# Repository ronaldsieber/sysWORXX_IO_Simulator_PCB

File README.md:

# sysWORXX IO Simulator

**KiCad Projekt des sysWORXX IO Simulator sowie Node-RED-Flow für das sysWORXX CTR-700, um die grundlegende Funktionalität des IO Simulator zu veranschaulichen.**

Der *sysWORXX IO Simulator* stellt verschiedene Peripherie-Elemente bereit, um Experimente sowie Test- und Inbetriebnahme von Softwareprojekten auf dem *sysWORXX CTR-700* zu vereinfachen.

## IO Simulator Board Features

Der *sysWORXX IO Simulator* umfasst folgende Peripherie-Elemente:
- 4x Digital Input 24V (Push-Button)
- 4x Digital Output 24V (LED)
- 4x Analog Input 0..10V (2x Poti, 1x Fotoelement, 1x Reflexkoppler)
- 1x A/B Encoder

![\[kicad_3d_model\]](Documentation/sysWORXX_IO_Simulator_PCB.3d-model.png)

## sysWORXX CTR-700

Der *sysWORXX CTR-700* ist ein Linux-basierter Controller mit offener Architektur, der softwareseitig stark dem Raspberry Pi ähnelt und die IO-Peripherie einer klassischen SPS-Steuerung unterstützt (DI/DO 24V, AI 0..10V, AI 4..20mA, Relais 230VAC, UART/RS232/RS485, ETH, CAN):

Hersteller Seite:
https://www.systec-electronic.com/produkte/industrial-internet-of-things/sysworxx-ctr-700

Bezugsquelle:
https://www.conrad.de/de/p/sysworxx-ctr-700-industrial-controller-industriesteuerung-sps-iot-leistungsstarke-steuerung-mqtt-node-red-805716248.html

![\[sysWORXX CTR-700\]](Documentation/sysWORXX_CTR-700.png)

Der CTR-700 unterstützt folgende Programmiersprachen:
- C/C++
- C#
- Java
- Python
- Node-RED
- IEC 61131-3

## sysWORXX IO Simulator

Der *sysWORXX IO Simulator* basiert auf einer vierlagigen Leiterplatte im Euro-Platinen Format (160x100 mm), von der jedoch nur 3 Ebenen benutz sind (Oberseite ohne Leiterbahnen). Die Platine ist einseitig bestückt und verwendet nur sehr einfach zu lötende THT Bauteile (Through Hole Technology). Der *IO Simulator* kann somit leicht auch von Schülern und Bastlern aufgebaut werden.

Die Werte aller Bauteile sind im [Schaltplan](Documentation/sysWORXX_IO_Simulator_PCB_Schematic.pdf) spezifiziert.

![\[sysWORXX IO Simulator\]](Documentation/sysWORXX_IO_Simulator.jpg)

**Verbindung zwischen IO Simulator und CTR-700**

Alle Anschlüsse des *IO Simulator* sind entsprechende ihrer Funktionalitäten gruppiert (DI, DO, AI, Enc). Die Beschriftung an den Schraubklemmenblöcken des *IO Simulator* entspricht exakt den Bezeichnungen am *CTR-700*. Es müssen einfach nur die Signale mit gleichen Bezeichnungen zwischen beiden Baugruppen verbunden werden.

![\[Connector\]](Documentation/sysWORXX_IO_Simulator_Connector.png)
| IO Simulator | -> | CTR-700 |
|--|--|--|
| IO Simulator [DI0] | -> | CTR-700 [DI0] |
| ... | -> | ... |
| IO Simulator [DI3] | -> | CTR-700 [DI3] |
| IO Simulator [DI14] | -> | CTR-700 [DI14] |
| IO Simulator [DI15] | -> | CTR-700 [DI15] |
| IO Simulator [DO0] | -> | CTR-700 [DO0] |
| ... | -> | ... |
| IO Simulator [DO3] | -> | CTR-700 [DO3] |
| IO Simulator [AI0] | -> | CTR-700 [AI0] |
| ... | -> | ... |
| IO Simulator [AI3] | -> | CTR-700 [AI3] |

Für den professionellen Einsatz als Industriesteuerung besitzt das *sysWORXX CTR-700* jeweils getrennte Spannungs-Domains für CPU-Teil (24V/GND), Digital In (24V/GND), Digital Out (24V/GND) und Analog In (GND). In typischen Test- und Experimentierumgebungen kommt jedoch nur ein 24V Netzteil zum Einsatz, aus dem alle Domains parallel versorgt werden (jeweils alle 24V Anschlüsse sowie alle GND Anschlüsse parallel geschalten). An diese Domain sind auch 24V und GND des *IO Simulator* mit anzubinden. 

**IO Simulator Details**

Die Peripherie für digitale Ein- und Ausgänge (Push-Button, LED, A/B Encoder) nutzt direkt die 24V Spannungsversorgung des *IO Simulators*. Für die Peripherie der analogen Eingänge stellt VR1 (78L12) eine eigene 12V Domain bereit. Die analogen Eingänge des *CTR-700* sind nominell für 0..10V spezifiziert, sie lösen jedoch bis 11.64V auf, um auch Übersteuerungen erkennen und behandeln zu können.

Das Board ist mit verschiedenfarbigen Tasterkappen und LEDs bestückt (siehe Foto oben). Bei den LEDs wird für die blaue LED D103 ein Vorwiderstand von 4k7 verwendet, während die Vorwiderstände der anderen 3 LEDs (D100/rot, D101/grün, D102/gelb) mit 2k4 nur etwa halb so groß dimensioniert sind. Dadurch wird die blaue LED D103 optisch in ihrer Helligkeit an die anderen, deutlich dunkleren LEDs angeglichen.

Der Zweig OPT1 (OPT1, R202, R212) kann mit einem Fotowiderstand vom Typ PDV-P8104 (wie im [Schaltplan](Documentation/sysWORXX_IO_Simulator_PCB_Schematic.pdf)  angegeben) oder alternativ mit einer Fotodiode vom Typ BPW34 bestückt werden. Je nach Variante ist der Wert von R202 entsprechend anzupassen:

| OPT1 | R202 |
|--|--|
| PDV-P8104 | 20k |
| BPW34 | 200k |

Das Footprint von OPT1 ist als Combi-Shape ausgeführt, auf dem sich sowohl ein Fotowiderstand PDV-P8104 als eine Fotodiode BPW34 bestücken lassen.

**KiCad Schaltplansymbole und Footprints**

Für den *sysWORXX IO Simulator* wurden einige Schaltplansymbole und Footprints neu erstellt bzw. modifiziert. Diese sind im Repository im Zweig [KiCad_Components/usrlib](KiCad_Components/usrlib) abgelegt.

**Bezugsquellen**

In der [Stückliste](Documentation/sysWORXX_IO_Simulator_PCB_BoM.pdf) (BoM, Bill of Material) sind für alle Komponenten mögliche Bezugsquellen (incl. Bestellnummer) angegeben. Bei einer Suche im Internet findet man zudem leicht mehrere PCB Hersteller, die direkt das KiCad Layout File *sysWORXX_IO_Simulator_PCB.kicad_pcb* importieren können. Die PCBs erhält man dann mit Bestückungsdruck auf der Oberseite nach wenigen Tagen per Post zugeschickt. Eine mögliche direkte Bezugsquelle der Platine ist z.B. hier:

https://aisler.net/p/VOPTYJUX

## Node-RED Inbetriebnahme-Software

Test- und Inbetriebnahme des *sysWORXX IO Simulator* unterstützt der Node-RED Flow [CTR-700_IO_Periphery.json](Node-RED_Flow/CTR-700_IO_Periphery.json). Er bedient alle Komponenten des Simulators und stellt die aktuellen Werte auf einem Dashboard dar.

![\[Node-RED Inbetriebnahme Flow\]](Documentation/Node-RED_Editor.png)

Der Node-RED Flow [CTR-700_IO_Periphery.json](Node-RED_Flow/CTR-700_IO_Periphery.json) ist wie folgt in das Node-RED auf dem *sysWORXX CTR-700* zu importieren:

    Node-RED Menu -> Import -> Zwischenablage -> Button "Select a File to Import"

Um den Inbetriebnahme Flow nutzen zu können, muss zusätzlich die Node-Bibliothek `node-red-contrib-ctr700-io` auf dem *CTR-700* installiert sein. Diese wird bei Bedarf wie folgt installiert:

    Node-RED Menu -> Palette verwalten -> Tab "installieren" -> im Suchfeld "node-red-contrib-ctr700-io" eintragen -> Suchergebnis markieren und installieren

Nach dem Deploy auf das *CTR-700* wird der Flow auf dem Gerät ausgeführt und das Node-RED Dashboard visualisiert die aktuellen Werte der IO-Peripherie.

![\[Node-RED Dashboard\]](Documentation/Node-RED_Dashboard.png)

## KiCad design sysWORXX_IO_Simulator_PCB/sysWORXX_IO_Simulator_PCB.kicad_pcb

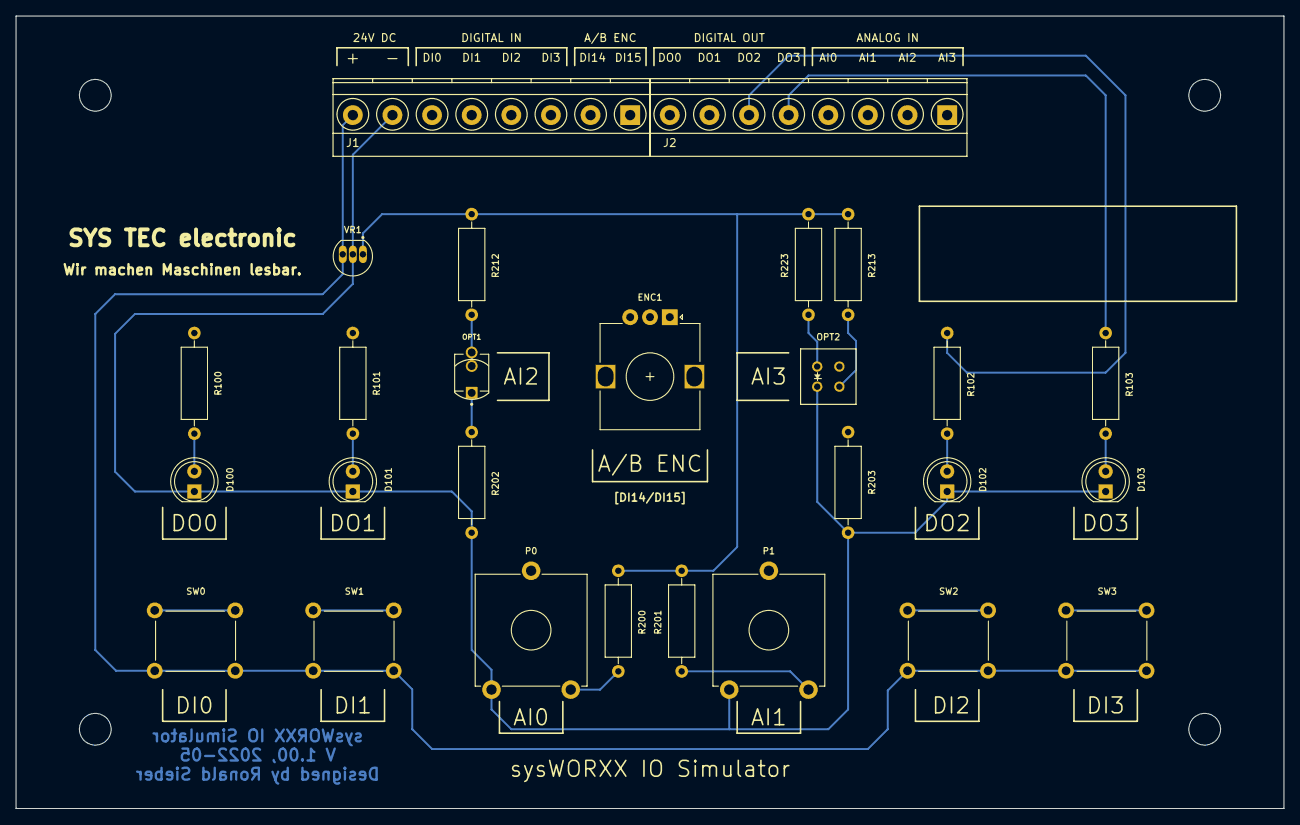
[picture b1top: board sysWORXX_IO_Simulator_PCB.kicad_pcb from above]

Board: 4 copper layers, 160.0 x 100.0 mm, 27 parts (0 on the bottom side), 26 nets.

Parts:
D100: DO0; LED_D5.0mm
D101: DO1; LED_D5.0mm
D102: DO2; LED_D5.0mm
D103: DO3; LED_D5.0mm
ENC1: EC12E; RotaryEncoder_Alps_EC12E_Vertical_H20mm
J1, J2: Conn_01x08; TerminalBlock_Phoenix_MKDS1.5-8pol
OPT1: PDV-P8104; BPW34_PDV-P8104_CombiShape
OPT2: CNY70; CNY70_DIP
P0, P1: 22k; Potentiometer_Trimmer_ACP_CA14v_Horizontal_Px15.0mm_Py10.0mm
R100, R101, R102: 2k4; R_Axial_DIN0309_L9.0mm_D3.2mm_P12.70mm_Horizontal
R103: 4k7; R_Axial_DIN0309_L9.0mm_D3.2mm_P12.70mm_Horizontal
R200, R201, R223: 1k; R_Axial_DIN0309_L9.0mm_D3.2mm_P12.70mm_Horizontal
R202: 20k; R_Axial_DIN0309_L9.0mm_D3.2mm_P12.70mm_Horizontal
R203: 47k; R_Axial_DIN0309_L9.0mm_D3.2mm_P12.70mm_Horizontal
R212, R213: 470R; R_Axial_DIN0309_L9.0mm_D3.2mm_P12.70mm_Horizontal
SW0: DI0; Multimec_5E_TH9
SW1: DI1; Multimec_5E_TH9
SW2: DI2; Multimec_5E_TH9
SW3: DI3; Multimec_5E_TH9
VR1: L78L12; TO92

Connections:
unnamed: D100.1, D101.1, D102.1, D103.1, J1.7, OPT2.2, P0.3, P1.3, R202.2, R203.2, VR1.2
unnamed: D100.2, R100.2
unnamed: D101.2, R101.2
unnamed: D102.2, R102.2
unnamed: D103.2, R103.2
unnamed: ENC1.A, J1.1
unnamed: ENC1.B, J1.2
unnamed: ENC1.C, J1.8, SW0.2, SW1.2, SW2.2, SW3.2, VR1.1
unnamed: J1.3, SW3.1
unnamed: J1.4, SW2.1
unnamed: J1.5, SW1.1
unnamed: J1.6, SW0.1
unnamed: J2.1, OPT2.4, R203.1
unnamed: J2.2, OPT1.1, R202.1
unnamed: J2.3, P1.2
unnamed: J2.4, P0.2
unnamed: J2.5, R103.1
unnamed: J2.6, R102.1
unnamed: J2.7, R101.1
unnamed: J2.8, R100.1
unnamed: OPT1.2, R212.2
unnamed: OPT2.1, R223.2
unnamed: OPT2.3, R213.2
unnamed: P0.1, R200.2
unnamed: P1.1, R201.2
unnamed: R200.1, R201.1, R212.1, R213.1, R223.1, VR1.3
